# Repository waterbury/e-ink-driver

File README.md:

### Open-source hardware design
----------

#### Introduction

E-ink driver board based on designs by @kennethlimcp and others..

swedishhat has a bunch of these: http://wiki.ai-thinker.com/esp32-s

#### Useful writeups 

- [Bringing up a new board from scratch](/Resources/bring-up.md)
- [Checking a new PCB and populating it](/Resources/pcb-checks.md)
- [EAGLE start off and mistakes](/Resources/eagle-notes.md)

#### Resources

- [Hardware product development process](http://conceptspring.com/hardware-product-development-process/)

- [Spark Proto2Prod website](http://www.proto2prod.com/)

- [EAGLE Help](http://web.mit.edu/xavid/arch/i386_rhel4/help/index.htm)

- [Sparkfun EAGLE Settings](https://github.com/sparkfun/SparkFun_Eagle_Settings)

- [3D Board viewer](http://3dbrdviewer.cytec.bg/)

- [KiCad Software](http://www.kicad-pcb.org/)

- [Systematic PCB verification](https://engineering.purdue.edu/ece477/Resources/SystematicPCBVerification.pdf)

- [7 fatal pcb mistakes to avoid by Make](http://makezine.com/2016/08/15/7-fatal-mistakes-avoid-printed-circuit-board-pcb-design/)

- [Board Level Electromagnetic Compatibility](http://www.nxp.com/files/microcontrollers/doc/app_note/AN2321.pdf)

- [The Dropout’s Guide to PCB Trace Antenna Design](http://colinkarpfinger.com/blog/2010/the-dropouts-guide-to-antenna-design/)

- [Antenna Design and RF Layout Guidelines](http://www.cypress.com/file/136236/download)

- [Converting Seeed OPL EagleCAD library to KiCad](https://www.seeed.cc/Converting%20Seeed%20OPL%20EagleCAD%20library%20to%20KiCad-p-1990.html)

- [Wireless Protocols for IoT Devices](http://glowlabs.co/wireless-protocols/)

- [Capacitor temperature and voltage variation](https://www.maximintegrated.com/en/app-notes/index.mvp/id/5527)

- [Minimizing Buck-Boost Converter High-Frequency Switching Noise](http://www.ti.com/lit/an/slva219a/slva219a.pdf)

- [CAN-bus Common High Speed Physical Layer Problems](https://vector.com/portal/medien/cmc/application_notes/AN-ANI-1-115_HS_Physical_Layer_Problems.pdf)

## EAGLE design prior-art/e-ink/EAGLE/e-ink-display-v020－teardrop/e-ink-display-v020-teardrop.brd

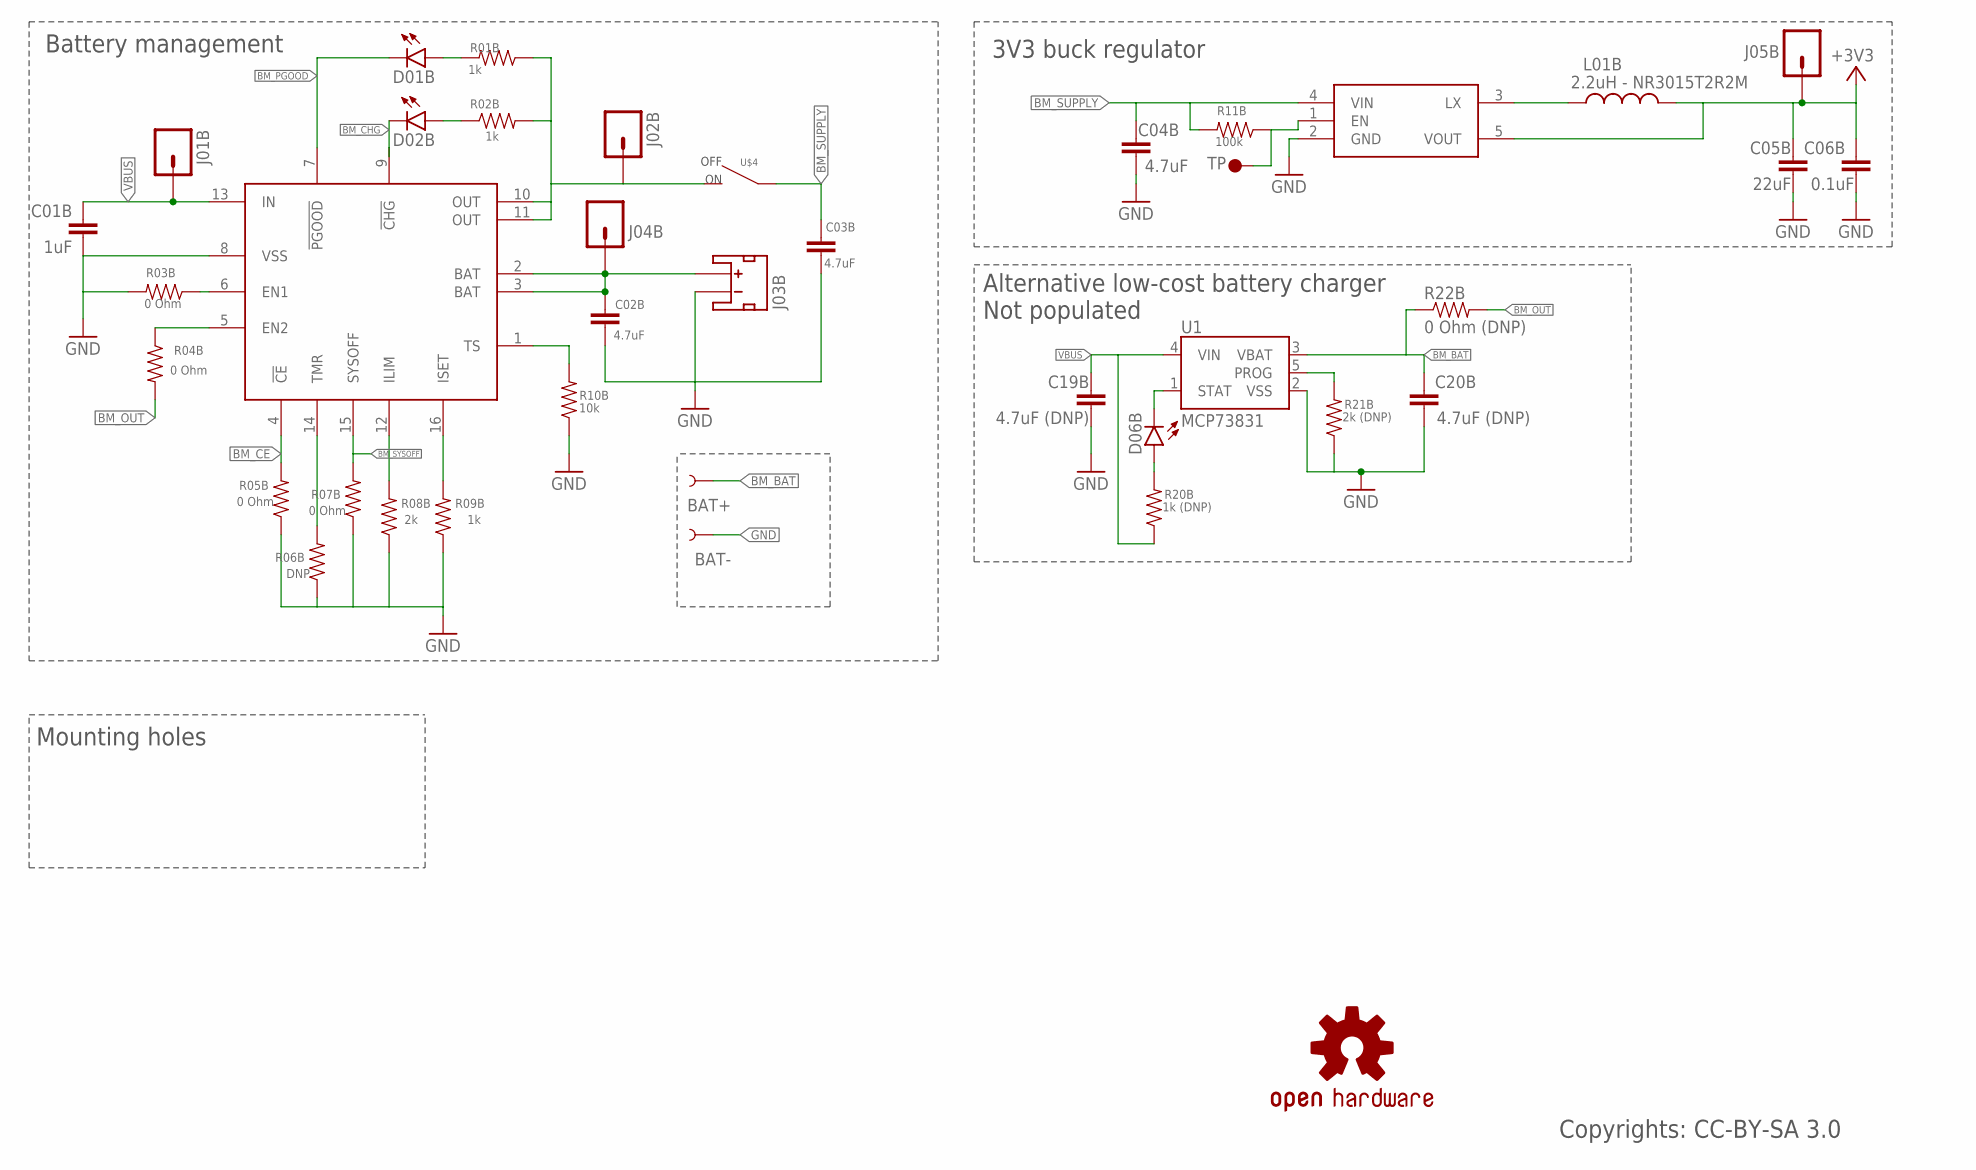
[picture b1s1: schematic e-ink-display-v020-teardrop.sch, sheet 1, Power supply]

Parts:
BAT+: TEST-POINTBOTH_SQ; TP_15_BOTH-SQ
BAT-: TEST-POINTBOTHBOTH; TP_15_BOTH
C01B: 1uF; 0603-CAP
C02B, C03B, C04B: 4.7uF; 0603-CAP
C05B: 22uF; 0603-CAP
C06B: 0.1uF; 0603-CAP
C19B, C20B: 4.7uF (DNP); 0603-CAP
D01B, D02B, D06B: LED0603; LED-0603
J01B, J02B, J04B, J05B: M01PTH; 1X01
J03B: JST_2MM_MALE; JST-2-SMD
L01B: 2.2uH - NR3015T2R2M; INDUCTOR-NR3015
LOGO1: OSHW-LOGOPAD; OSHW-LOGO-M-PAD
R01B, R02B, R09B: 1k; 0603-RES
R03B, R04B, R05B, R07B: 0 Ohm; 0603-RES
R06B: DNP; 0603-RES
R08B: 2k; 0603-RES
R10B: 10k; 0603-RES
R11B: 100k; 0603-RES
R20B: 1k (DNP); 0603-RES
R21B: 2k (DNP); 0603-RES
R22B: 0 Ohm (DNP); 1206
TP01B: TP1; TP35_BOT
U1: MCP73831; SOT23-5
U01B: BQ24075; PVQFN-16
U02B: R8008-33; SOT23-5
U$4: SWITCHSLIDE; CHANGE_OVER_SLIDE

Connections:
+3V3: C05B.2, C06B.2, J05B.1, L01B.2, U02B.5 (VOUT); also elsewhere on the board
BM_BAT: BAT+.P$1, C02B.2, C20B.2, J03B.2 (+), J04B.1, R22B.1, U1.3 (VBAT), U01B.2 (BAT), U01B.3 (BAT)
BM_CE: R05B.2, U01B.4 (!CE)
BM_CHG: D02B.C, U01B.9 (!CHG); also elsewhere on the board
BM_OUT: J02B.1, R01B.1, R02B.2, R04B.2, R22B.2, U01B.10 (OUT), U01B.11 (OUT), U$4.2
BM_PGOOD: D01B.C, U01B.7 (!PGOOD); also elsewhere on the board
BM_SUPPLY: C03B.2, C04B.2, R11B.2, U02B.4 (VIN), U$4.1; also elsewhere on the board
BM_SYSOFF: R07B.2, U01B.15 (SYSOFF)
GND: BAT-.P$1, C01B.1, C02B.1, C03B.1, C04B.1, C05B.1, C06B.1, C19B.1, C20B.1, J03B.1 (-), R03B.2, R05B.1, R06B.1, R07B.1, R08B.1, R09B.1, R10B.1, R21B.1, U1.2 (VSS), U01B.8 (VSS), U02B.2 (GND); also elsewhere on the board
unnamed: R08B.2, U01B.12 (ILIM)
unnamed: R09B.2, U01B.16 (ISET)
unnamed: R04B.1, U01B.5 (EN2)
unnamed: R03B.1, U01B.6 (EN1)
unnamed: R06B.2, U01B.14 (TMR)
unnamed: R10B.2, U01B.1 (TS)
unnamed: D02B.A, R02B.1
unnamed: D01B.A, R01B.2
unnamed: R21B.2, U1.5 (PROG)
unnamed: R11B.1, TP01B.P$1, U02B.1 (EN)
unnamed: L01B.1, U02B.3 (LX)
unnamed: D06B.C, U1.1 (STAT)
unnamed: D06B.A, R20B.2
VBUS: C01B.2, C19B.2, J01B.1, R20B.1, U1.4 (VIN), U01B.13 (IN); also elsewhere on the board

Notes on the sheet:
Battery management
3V3 buck regulator
Mounting holes
Alternative low-cost battery charger Not populated
Copyrights: CC-BY-SA 3.0

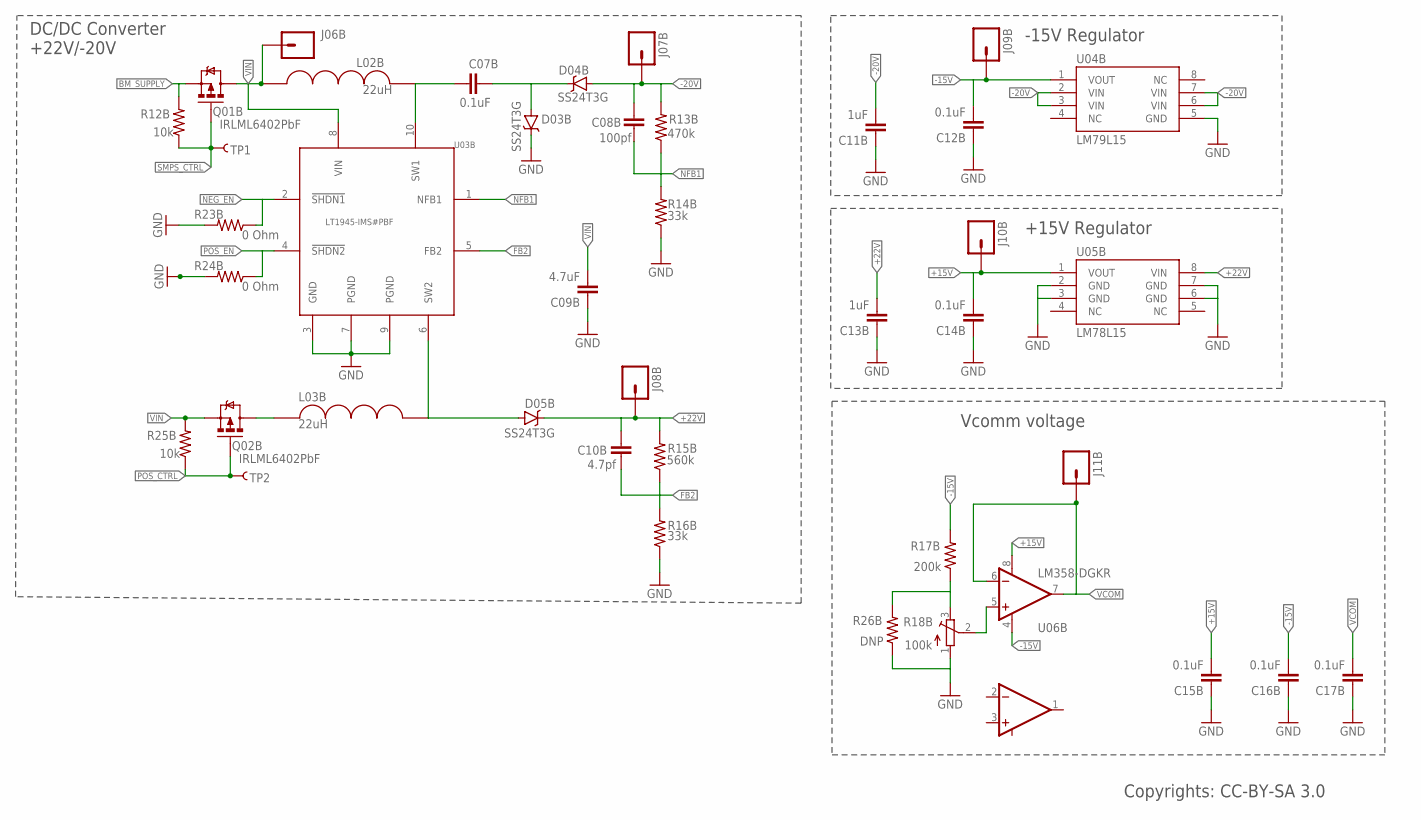
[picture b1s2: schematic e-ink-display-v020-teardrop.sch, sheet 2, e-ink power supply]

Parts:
C07B, C12B, C14B, C15B, C16B, C17B: 0.1uF; 0603-CAP
C08B: 100pf; 0603-CAP
C09B: 4.7uF; 0603-CAP
C10B: 4.7pf; 0603-CAP
C11B, C13B: 1uF; 0603-CAP
D03B, D04B, D05B: SS24T3G; SMA-DIODE
J06B, J07B, J08B, J09B, J10B, J11B: M01PTH; 1X01
L02B, L03B: 22uH; 4040(1515)
Q01B, Q02B: IRLML6402PbF; SOT23-3
R12B, R25B: 10k; 0603-RES
R13B: 470k; 0603-RES
R14B, R16B: 33k; 0603-RES
R15B: 560k; 0603-RES
R17B: 200k; 0603-RES
R18B: 100k; TC33X
R23B, R24B: 0 Ohm; 0603-RES
R26B: DNP; 0603-RES
TP1, TP2: TEST-POINTBOTHBOTH; TP_15_BOTH
U03B: LT1945-IMS#PBF; MSOP-10
U04B: LM79L15; SO08
U05B: LM78L15; SO08
U06B: LM358-DGKR; MSOP-8

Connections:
+15V: C14B.2, C15B.2, J10B.1, U05B.1 (VOUT), U06B.8 (V+); also elsewhere on the board
+22V: C10B.2, C13B.2, D05B.C, J08B.1, R15B.2, U05B.8 (VIN); also elsewhere on the board
-15V: C12B.2, C16B.2, J09B.1, R17B.2, U04B.1 (VOUT), U06B.4 (V-); also elsewhere on the board
-20V: C08B.2, C11B.2, D04B.A, J07B.1, R13B.2, U04B.2 (VIN), U04B.3 (VIN), U04B.6 (VIN), U04B.7 (VIN); also elsewhere on the board
BM_SUPPLY: Q01B.2 (S), R12B.2; also elsewhere on the board
FB2: C10B.1, R15B.1, R16B.2, U03B.5 (FB2)
GND: C09B.1, C11B.1, C12B.1, C13B.1, C14B.1, C15B.1, C16B.1, C17B.1, D03B.C, R14B.1, R16B.1, R18B.1 (A), R23B.2, R24B.2, R26B.1, U03B.3 (GND), U03B.7 (PGND), U03B.9 (PGND), U04B.5 (GND), U05B.2 (GND), U05B.3 (GND), U05B.6 (GND), U05B.7 (GND); also elsewhere on the board
unnamed: C07B.1, L02B.P$2, U03B.10 (SW1)
unnamed: C07B.2, D03B.A, D04B.C
unnamed: R18B.2 (S), U06B.5 (+IN2)
unnamed: D05B.A, L03B.P$2, U03B.6 (SW2)
unnamed: L03B.P$1, Q02B.3 (D)
unnamed: R17B.1, R18B.3 (E), R26B.2
NEG_EN: R23B.1, U03B.2 (!SHDN1); also elsewhere on the board
NFB1: C08B.1, R13B.1, R14B.2, U03B.1 (NFB1)
POS_CTRL: Q02B.1 (G), R25B.1, TP2.P$1; also elsewhere on the board
POS_EN: R24B.1, U03B.4 (!SHDN2); also elsewhere on the board
SMPS_CTRL: Q01B.1 (G), R12B.1, TP1.P$1; also elsewhere on the board
VCOM: C17B.2, J11B.1, U06B.6 (-IN2), U06B.7 (OUT2); also elsewhere on the board
VIN: C09B.2, J06B.1, L02B.P$1, Q01B.3 (D), Q02B.2 (S), R25B.2, U03B.8 (VIN)

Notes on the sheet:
-15V Regulator
+15V Regulator
Vcomm voltage
DC/DC Converter +22V/-20V
Copyrights: CC-BY-SA 3.0

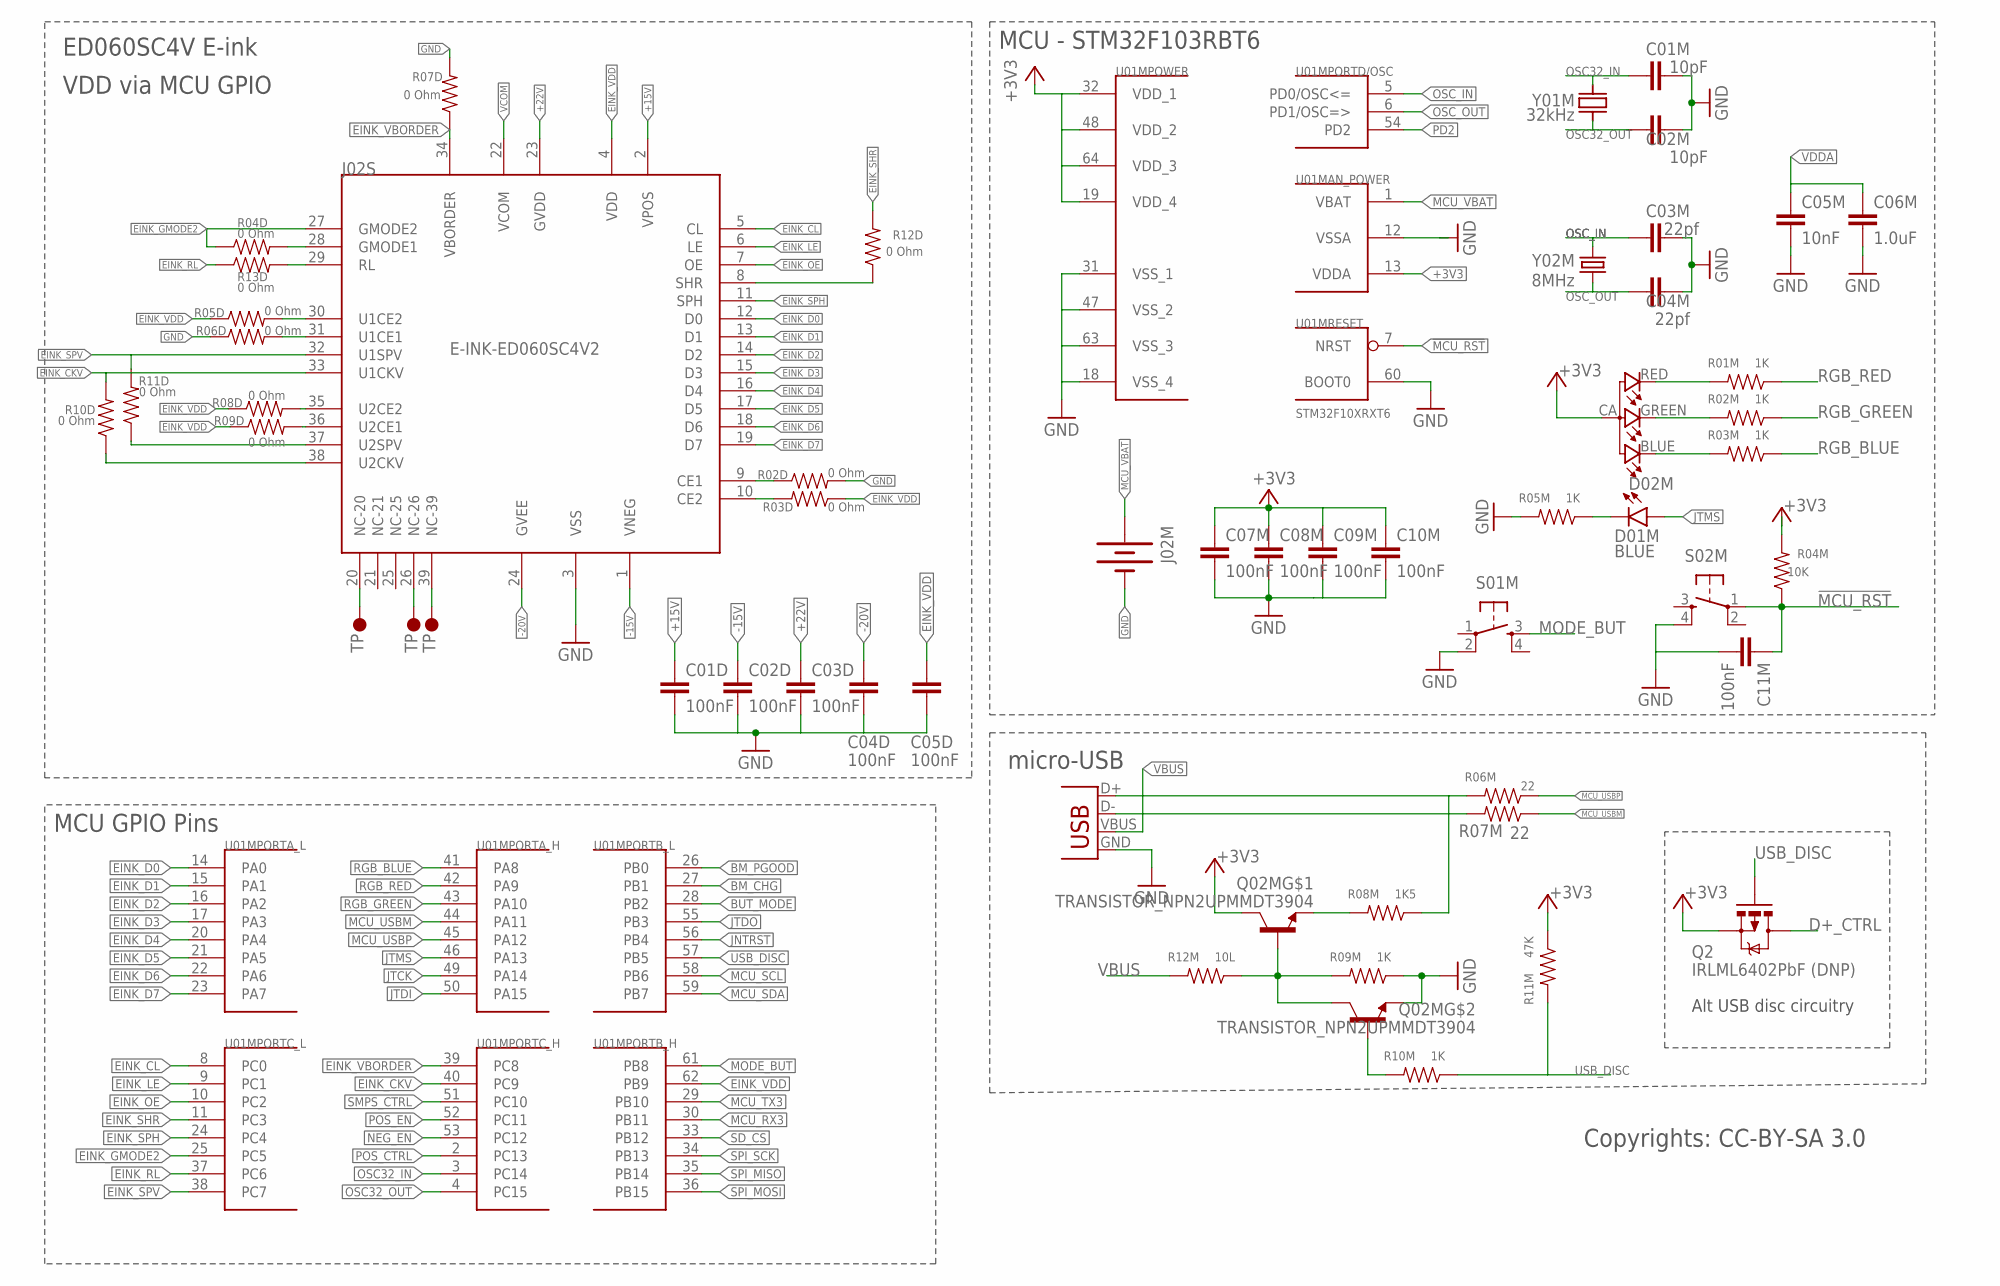
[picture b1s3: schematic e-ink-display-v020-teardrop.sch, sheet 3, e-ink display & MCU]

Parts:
C01D, C02D, C03D, C04D, C05D, C07M, C08M, C09M, C10M, C11M: 100nF; 0603-CAP
C01M, C02M: 10pF; 0603-CAP
C03M, C04M: 22pf; 0603-CAP
C05M: 10nF; 0603-CAP
C06M: 1.0uF; 0603-CAP
D01M: BLUE; LED-0603
D02M: RGB-LED-CLMVB-FKARGB; PLCC4-2MM-RGB
J01M: USBUSB-MICROB-PAD-EXTEND; USB-MICROB-SLOT-HOLE-EXTEND
J02M: BATTERY20PTH; BATTCOM_20MM_PTH
J02S: E-INK-ED060SC4V2; FPC-0.3-39
Q2: IRLML6402PbF (DNP); SOT23-3
Q02M: TRANSISTOR_NPN2UPMMDT3904; SOT363
R01M, R02M, R03M, R05M, R09M, R10M: 1K; 0603-RES
R02D, R03D, R04D, R05D, R06D, R07D, R08D, R09D, R10D, R11D, R12D, R13D: 0 Ohm; 0603-RES
R04M: 10K; 0603-RES
R06M, R07M: 22; 0603-RES
R08M: 1K5; 0603-RES
R11M: 47K; 0603-RES
R12M: 10L; 0603-RES
S01M, S02M: TAC_SWITCHSMD; TACTILE_SWITCH_SMD
U01M: STM32F10XRXT6; TQFP64
U$1, U$8, U$9: TP1; TP35_BOT
Y01M: 32kHz; FC135
Y02M: 8MHz; CRYSTAL-SMD-5X3

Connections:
!MCU_RST: C11M.1, R04M.1, S02M.1, U01M.7 (NRST); also elsewhere on the board
+3V3: C07M.1, C08M.1, C09M.1, C10M.1, D02M.CA (1), Q2.2 (S), Q02M.6 (C), R04M.2, R11M.1, U01M.13 (VDDA), U01M.19 (VDD_4), U01M.32 (VDD_1), U01M.48 (VDD_2), U01M.64 (VDD_3); also elsewhere on the board
+15V: C01D.1, J02S.2 (VPOS); also elsewhere on the board
+22V: C03D.1, J02S.23 (GVDD); also elsewhere on the board
-15V: C02D.1, J02S.1 (VNEG); also elsewhere on the board
-20V: C04D.1, J02S.24 (GVEE); also elsewhere on the board
BM_CHG: U01M.27 (PB1); also elsewhere on the board
BM_PGOOD: U01M.26 (PB0); also elsewhere on the board
BUT_MODE: U01M.28 (PB2)
CE2: J02S.10 (CE2), R03D.2
D+_CTRL: Q2.3 (D), Q02M.1 (E), R08M.2
EINK_CKV: J02S.33 (U1CKV), R10D.2, U01M.40 (PC9); also elsewhere on the board
EINK_CL: J02S.5 (CL), U01M.8 (PC0); also elsewhere on the board
EINK_D0: J02S.12 (D0), U01M.14 (PA0); also elsewhere on the board
EINK_D1: J02S.13 (D1), U01M.15 (PA1); also elsewhere on the board
EINK_D2: J02S.14 (D2), U01M.16 (PA2); also elsewhere on the board
EINK_D3: J02S.15 (D3), U01M.17 (PA3); also elsewhere on the board
EINK_D4: J02S.16 (D4), U01M.20 (PA4); also elsewhere on the board
EINK_D5: J02S.17 (D5), U01M.21 (PA5); also elsewhere on the board
EINK_D6: J02S.18 (D6), U01M.22 (PA6); also elsewhere on the board
EINK_D7: J02S.19 (D7), U01M.23 (PA7); also elsewhere on the board
EINK_GMODE2: J02S.27 (GMODE2), R04D.1, U01M.25 (PC5); also elsewhere on the board
EINK_LE: J02S.6 (LE), U01M.9 (PC1); also elsewhere on the board
EINK_OE: J02S.7 (OE), U01M.10 (PC2); also elsewhere on the board
EINK_RL: R13D.1, U01M.37 (PC6); also elsewhere on the board
EINK_SHR: R12D.2, U01M.11 (PC3); also elsewhere on the board
EINK_SPH: J02S.11 (SPH), U01M.24 (PC4); also elsewhere on the board
EINK_SPV: J02S.32 (U1SPV), R11D.2, U01M.38 (PC7); also elsewhere on the board
EINK_VBORDER: J02S.34 (VBORDER), R07D.1, U01M.39 (PC8); also elsewhere on the board
EINK_VDD: C05D.1, J02S.4 (VDD), R03D.1, R05D.1, R08D.1, R09D.1, U01M.62 (PB9); also elsewhere on the board
GND: C01D.2, C01M.2, C02D.2, C02M.2, C03D.2, C03M.2, C04D.2, C04M.2, C05D.2, C05M.2, C06M.2, C07M.2, C08M.2, C09M.2, C10M.2, C11M.2, J01M.GND, J02M.2 (-), J02S.3 (VSS), Q02M.4 (E), R02D.2, R05M.2, R06D.1, R07D.2, R09M.1, S01M.2, S02M.4, U01M.12 (VSSA), U01M.18 (VSS_4), U01M.31 (VSS_1), U01M.47 (VSS_2), U01M.60 (BOOT0), U01M.63 (VSS_3); also elsewhere on the board
JNTRST: U01M.56 (PB4); also elsewhere on the board
JTCK: U01M.49 (PA14); also elsewhere on the board
JTDI: U01M.50 (PA15); also elsewhere on the board
JTDO: U01M.55 (PB3); also elsewhere on the board
JTMS: D01M.A, U01M.46 (PA13); also elsewhere on the board
MCU_RX3: U01M.30 (PB11); also elsewhere on the board
MCU_SCL: U01M.58 (PB6); also elsewhere on the board
MCU_SDA: U01M.59 (PB7); also elsewhere on the board
MCU_TX3: U01M.29 (PB10); also elsewhere on the board
MCU_USBM: R07M.1, U01M.44 (PA11)
MCU_USBP: R06M.1, U01M.45 (PA12)
MCU_VBAT: J02M.1 (+), U01M.1 (VBAT)
MODE_BUT: S01M.3, U01M.61 (PB8)
N$: J01M.D+, R06M.2, R08M.1
unnamed: J02S.28 (GMODE1), R04D.2
unnamed: J02S.31 (U1CE1), R06D.2
unnamed: D02M.RED (4), R01M.2
unnamed: Q02M.2 (B), Q02M.3 (C), R09M.2, R12M.1
unnamed: J02S.29 (RL), R13D.2
unnamed: J02S.35 (U2CE2), R08D.2
unnamed: J02S.36 (U2CE1), R09D.2
unnamed: J02S.9 (CE1), R02D.1
unnamed: J02S.20 (NC-20), U$1.P$1
unnamed: J02S.26 (NC-26), U$8.P$1
unnamed: J02S.8 (SHR), R12D.1
unnamed: J02S.39 (NC-39), U$9.P$1
unnamed: Q02M.5 (B), R10M.2
unnamed: D01M.C, R05M.1
unnamed: J01M.D-, R07M.2
NEG_EN: U01M.53 (PC12); also elsewhere on the board
OSC32_IN: C01M.1, U01M.3 (PC14), Y01M.X2 (2)
OSC32_OUT: C02M.1, U01M.4 (PC15), Y01M.X1 (1)
OSC_IN: C03M.1, U01M.5 (PD0/OSC<=), Y02M.3 (2)
OSC_OUT: C04M.1, U01M.6 (PD1/OSC=>), Y02M.1
PD2: U01M.54 (PD2)
POS_CTRL: U01M.2 (PC13); also elsewhere on the board
POS_EN: U01M.52 (PC11); also elsewhere on the board
R02M: D02M.GREEN (3), R02M.2
R03M: D02M.BLUE (2), R03M.2
RGB_BLUE: R03M.1, U01M.41 (PA8)
RGB_GREEN: R02M.1, U01M.43 (PA10)
RGB_RED: R01M.1, U01M.42 (PA9)
SD_CS: U01M.33 (PB12); also elsewhere on the board
SMPS_CTRL: U01M.51 (PC10); also elsewhere on the board
SPI_MISO: U01M.35 (PB14); also elsewhere on the board
SPI_MOSI: U01M.36 (PB15); also elsewhere on the board
SPI_SCK: U01M.34 (PB13); also elsewhere on the board
U1CE2: J02S.30 (U1CE2), R05D.2
U2CKV: J02S.38 (U2CKV), R10D.1
U2SPV: J02S.37 (U2SPV), R11D.1
USB_DISC: Q2.1 (G), R10M.1, R11M.2, U01M.57 (PB5); also elsewhere on the board
VBUS: J01M.VBUS, R12M.2; also elsewhere on the board
VCOM: J02S.22 (VCOM); also elsewhere on the board
VDDA: C05M.1, C06M.1

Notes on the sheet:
ED060SC4V E-ink VDD via MCU GPIO
MCU - STM32F103RBT6
Copyrights: CC-BY-SA 3.0
micro-USB
MCU GPIO Pins
Alt USB disc circuitry

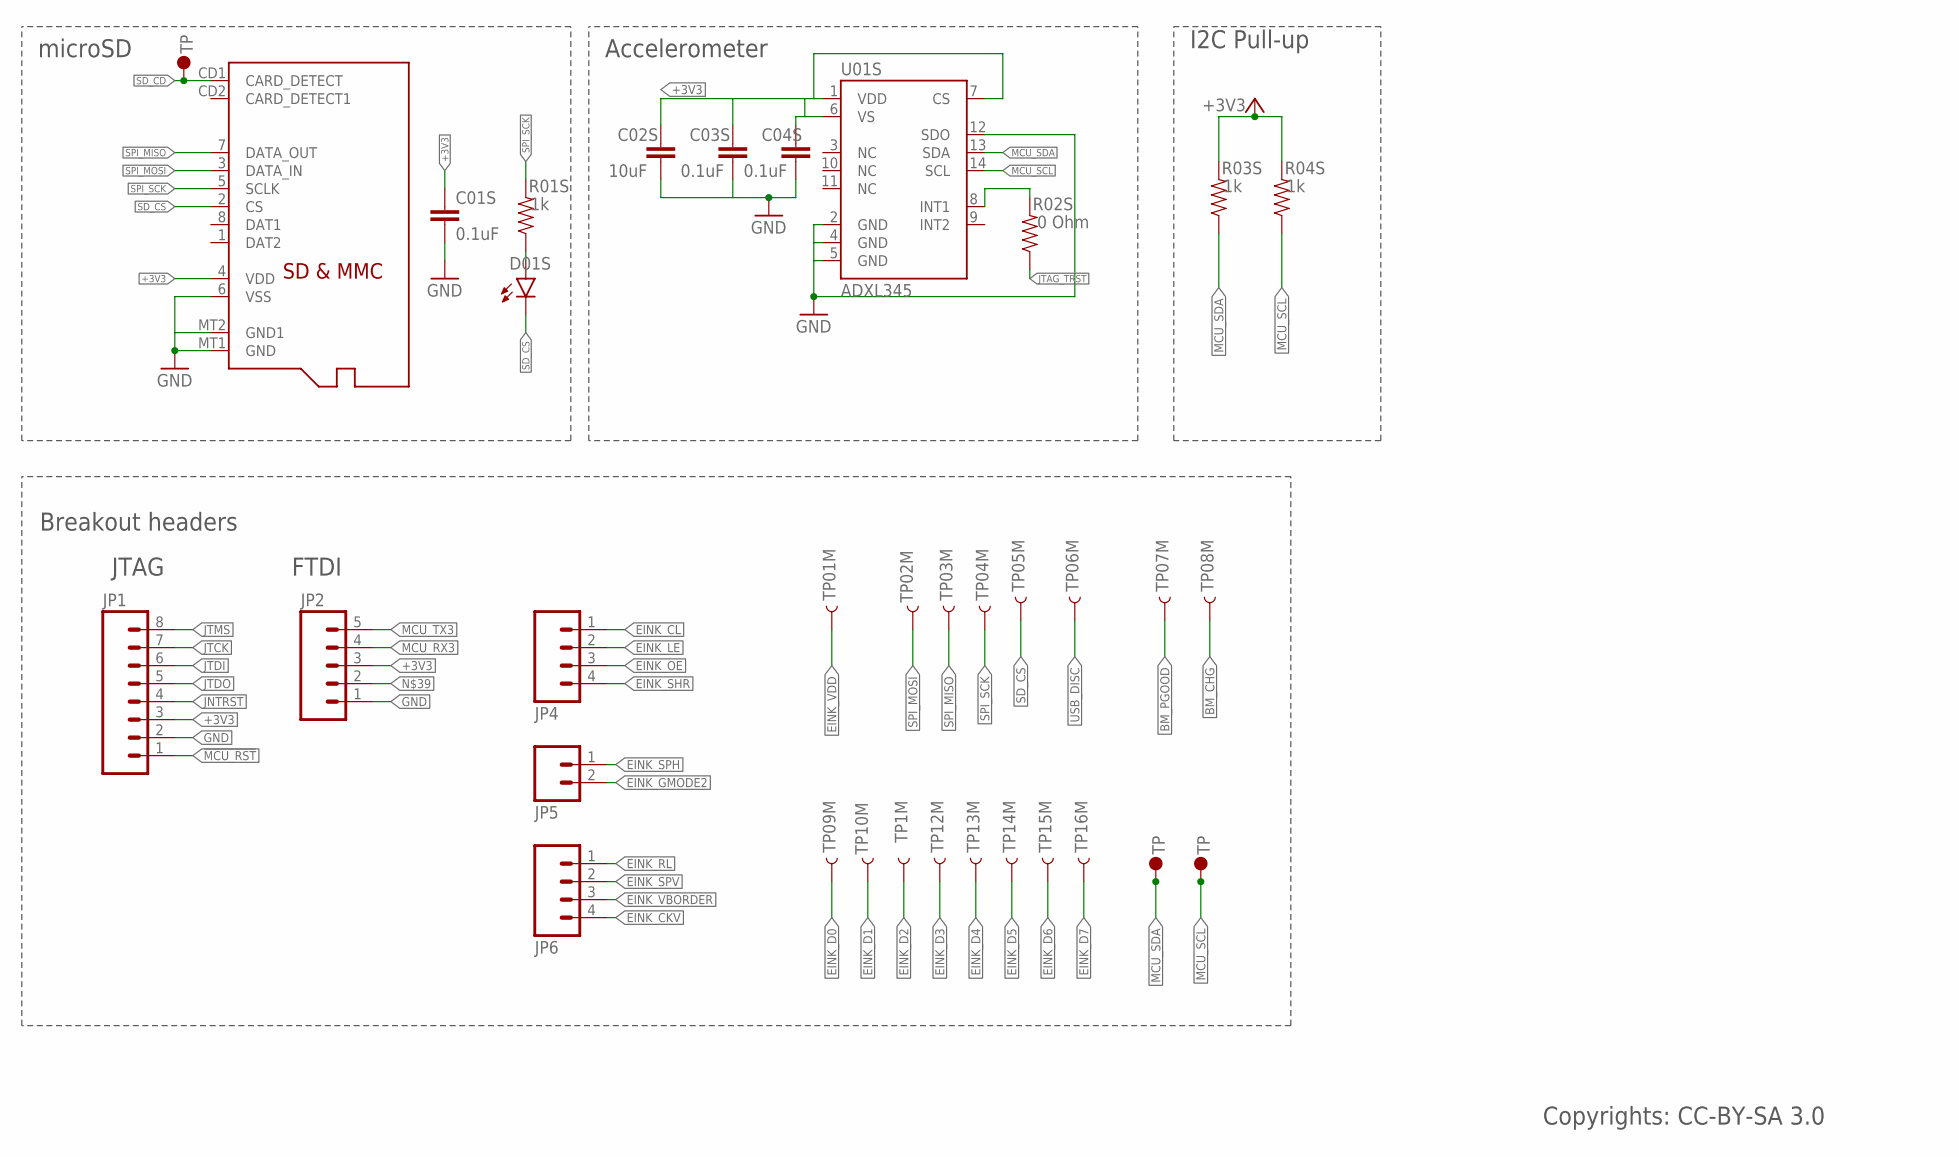
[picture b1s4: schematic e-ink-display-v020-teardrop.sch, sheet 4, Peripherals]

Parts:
C01S, C03S, C04S: 0.1uF; 0603-CAP
C02S: 10uF; 0603-CAP
D01S: LED0603; LED-0603
J01S: MICROSD
JP1: M08; 1X08_ROUND
JP2: M05PTH; 1X05
JP4, JP6: M04PTH; 1X04
JP5: M02PTH; 1X02
R01S, R03S, R04S: 1k; 0603-RES
R02S: 0 Ohm; 0603-RES
TP01M, TP1M, TP02M, TP04M, TP05M, TP06M, TP07M, TP08M, TP09M, TP10M, TP12M, TP13M, TP14M, TP15M, TP16M: TEST-POINTBOTHBOTH; TP_15_BOTH
TP03M: TEST-POINTTP_15TH_THRU; TP_15TH
TP17M, TP18M: TP1; TP35_BOT
U01S: ADXL345; LGA14
U$5: TP3; TP60_BOT

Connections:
!MCU_RST: JP1.1; also elsewhere on the board
+3V3: C01S.1, C02S.1, C03S.1, C04S.1, J01S.4 (VDD), JP1.3, JP2.3, R03S.2, R04S.2, U01S.1 (VDD), U01S.6 (VS), U01S.7 (CS); also elsewhere on the board
BM_CHG: TP08M.P$1; also elsewhere on the board
BM_PGOOD: TP07M.P$1; also elsewhere on the board
EINK_CKV: JP6.4; also elsewhere on the board
EINK_CL: JP4.1; also elsewhere on the board
EINK_D0: TP09M.P$1; also elsewhere on the board
EINK_D1: TP10M.P$1; also elsewhere on the board
EINK_D2: TP1M.P$1; also elsewhere on the board
EINK_D3: TP12M.P$1; also elsewhere on the board
EINK_D4: TP13M.P$1; also elsewhere on the board
EINK_D5: TP14M.P$1; also elsewhere on the board
EINK_D6: TP15M.P$1; also elsewhere on the board
EINK_D7: TP16M.P$1; also elsewhere on the board
EINK_GMODE2: JP5.2; also elsewhere on the board
EINK_LE: JP4.2; also elsewhere on the board
EINK_OE: JP4.3; also elsewhere on the board
EINK_RL: JP6.1; also elsewhere on the board
EINK_SHR: JP4.4; also elsewhere on the board
EINK_SPH: JP5.1; also elsewhere on the board
EINK_SPV: JP6.2; also elsewhere on the board
EINK_VBORDER: JP6.3; also elsewhere on the board
EINK_VDD: TP01M.P$1; also elsewhere on the board
GND: C01S.2, C02S.2, C03S.2, C04S.2, J01S.6 (VSS), J01S.MT1 (GND), J01S.MT2 (GND1), JP1.2, JP2.1, U01S.2 (GND), U01S.4 (GND), U01S.5 (GND), U01S.12 (SDO); also elsewhere on the board
JNTRST: JP1.4; also elsewhere on the board
JTAG_TRST: R02S.1
JTCK: JP1.7; also elsewhere on the board
JTDI: JP1.6; also elsewhere on the board
JTDO: JP1.5; also elsewhere on the board
JTMS: JP1.8; also elsewhere on the board
MCU_RX3: JP2.4; also elsewhere on the board
MCU_SCL: R04S.1, TP18M.P$1, U01S.14 (SCL); also elsewhere on the board
MCU_SDA: R03S.1, TP17M.P$1, U01S.13 (SDA); also elsewhere on the board
MCU_TX3: JP2.5; also elsewhere on the board
unnamed: R02S.2, U01S.8 (INT1)
R01S: D01S.A, R01S.1
SD_CD: J01S.CD1 (CARD_DETECT), U$5.P$1
SD_CS: D01S.C, J01S.2 (CS), TP05M.P$1; also elsewhere on the board
SPI_MISO: J01S.7 (DATA_OUT), TP03M.P$1; also elsewhere on the board
SPI_MOSI: J01S.3 (DATA_IN), TP02M.P$1; also elsewhere on the board
SPI_SCK: J01S.5 (SCLK), R01S.2, TP04M.P$1; also elsewhere on the board
USB_DISC: TP06M.P$1; also elsewhere on the board

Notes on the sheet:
microSD
Accelerometer
Copyrights: CC-BY-SA 3.0
I2C Pull-up
JTAG
FTDI
Breakout headers

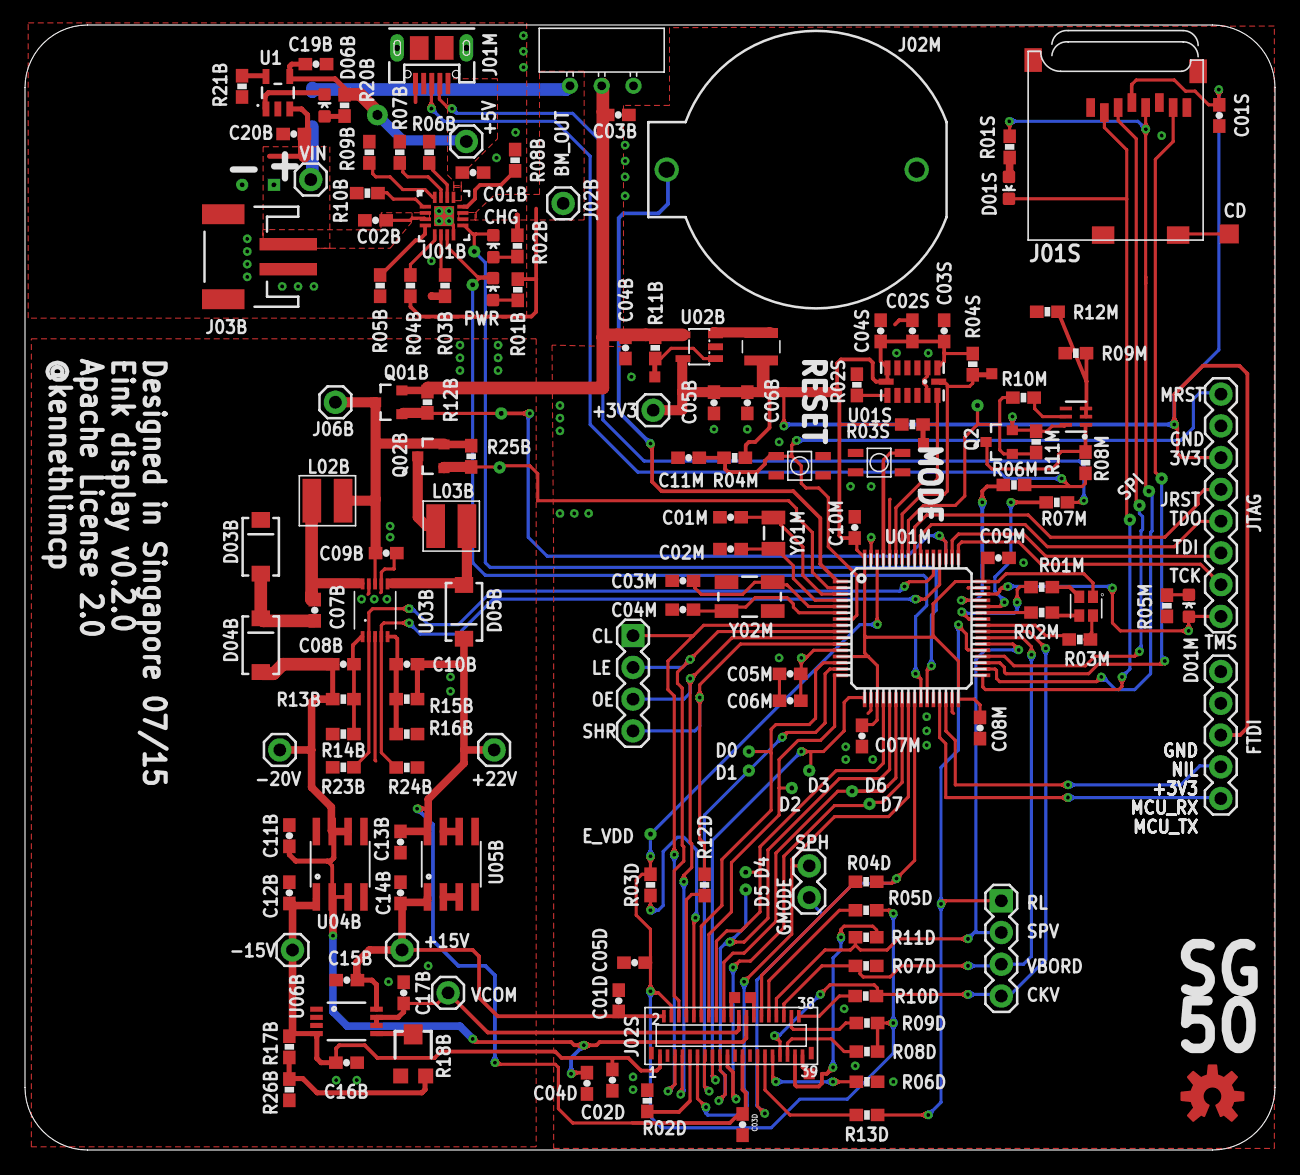
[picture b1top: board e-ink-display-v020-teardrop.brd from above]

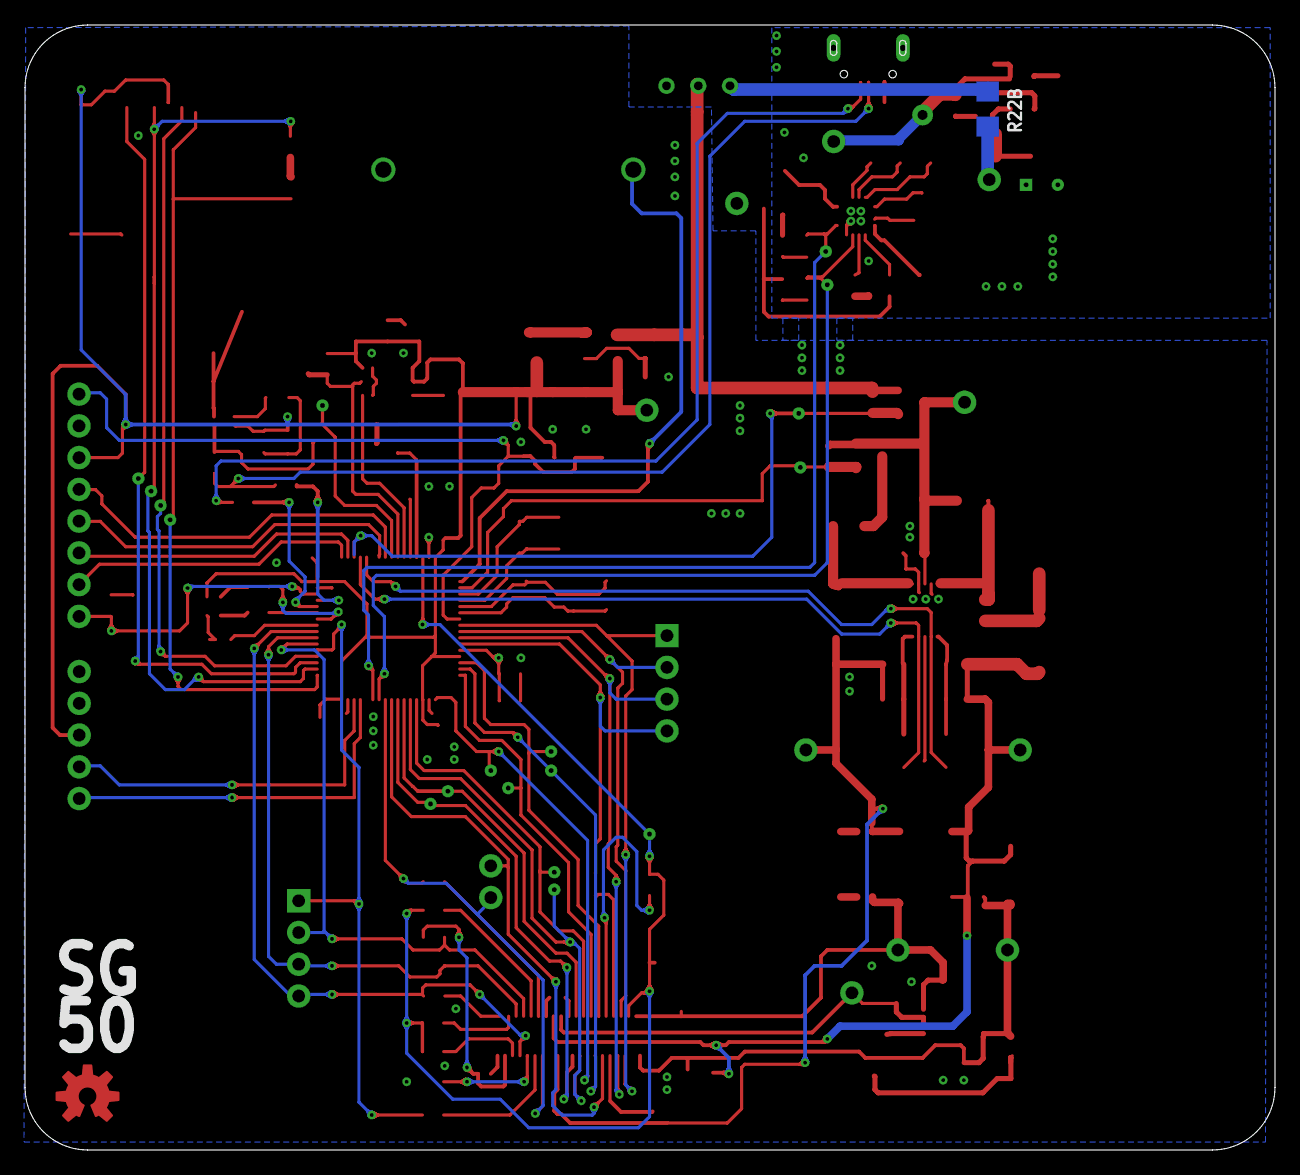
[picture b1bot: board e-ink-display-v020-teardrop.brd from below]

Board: 4 copper layers, 100.0 x 90.0 mm, 170 parts (8 on the bottom side), 113 nets.

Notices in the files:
prior-art/e-ink/EAGLE/e-ink-display-v010/e-ink-display-v010.brd:
Apache License 2.0
parts and their libraries:
SparkFun-Capacitors: Licensing: Creative Commons ShareAlike 4.0 International - https://creativecommons.org/licenses/by-sa/4.0
